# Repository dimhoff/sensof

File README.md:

# Sensof
Si4010 based wireless sensors(temperature, humidity, etc.) firmware and utilities.

**Project status**: This project is not actively maintained other then some
minor fixes to keep it working for myself.

# Sensof-HT
Sensof-HT is a temperature and humidity sensor that is build using a Si4010 MCU
and a HTU21 sensor.

## Circuit diagram
The Si4010 connects to a HTU21D, Si7020 or compatible sensor through I2C. The
I2C bus is connected to the Si4010 on the following pins:

   GPIO1 = SCL
   GPIO2 = SDA

Voltage level should be between 3.6 - 1.9 Volt. A 3V CR2032 works fine.

Some ready made Si4010 and HTU21D or Si7020 sensor are available on the
internet. These only need to be connected together and connected to a battery.

This repository also contains a custom Sensof-HT PCB. However this is currently
still under development. See hardware/README.md for more information.

## RF communication
The system uses the following modulation/encoding settings:

- Modulation: FSK
- Center Freq: 433.92 MHz
- FSK Deviation: 59 kHz
- Data rate: 9.6 kbits/s
- Encoding: NRZ Only (eg. no encoding)

## Receiver
I use a RFM22B module, which is based on the Si4430 transceiver,
connected to a Raspberry Pi for receiving the signal. The source code of the
receiving program is available in the software/si443x_sensof directory.

I also did some experiments with a SX1231 based module. Which seem to have a
better reception. I don't have any example code for this available in the
source tree.

# Sensof Frame Format
The Sensof frames are compatible with the Si4430/EZRadioPro receiver, and have
the following structure:

    +-----------+-----------+--------------+------------+
    | Preamble  | Sync Word | Enc. Payload | CRC-16-IBM |
    | 13 * 0xaa | 0x2d 0xd4 |   16-byte    |   2-byte   |
    +-----------+-----------+--------------+------------+

The CRC-16 uses the 0x8005 polynomial. The payload is a single AES-128
encrypted block, see [Encrypted Payload].

## Encrypted Payload
The payload is encrypted using AES-128 in ECB mode. To make this secure
against various attacks some mandatory field within the encrypted block have
been defined. The payload is formatted as follows:

    +---------+----------+------------------+
    | Dev. ID | Frame ID | Application data |
    | 4-byte  |  4-byte  |      8-byte      |
    +---------+----------+------------------+

The device ID identifies the source of the message. The Si4010 32-bit uniq
chip ID shall be used for this. The receiver will ignore frames that are from
an unknown source.

The 32-bit frame ID uniquely identifies the frame and allows duplicate frame
detection. The frame ID will be incremented sequentially, starting at 0. The
receiver must only accept frames with a frame ID above the last received frame
ID, and which is a 'reasonable amount higher' than the previous frame ID. See
the [Sensof Security Rational] chapter to get an indication of what a
'reasonable amount higher' means.

The remaining 8 byte can be used for application specific data. It is not
possible to have more or less then 8-byte payload in a single frame. If less
bytes are required the remaining bytes must be set to a known default. For
security reasons the receiver must verify these bytes. If more then 8 bytes
payload are required the payload must be split across multiple frames.

A full explanation of the security model is described below in [Sensof Security
Rational].

## Sensof-HT Frame Payload
The Sensof-HT frames contain the following payload:

 - Temperature(uint16_t): Temperature value as returned by HTU21 IC
 - Humidity(uint16_t): Humidity value as returned by HTU21 IC
 - Padding(uint32_t): '0' padding

See the HTU21 datasheet for the formulas to convert the temperature and
humidity to human readable values.

## SI4430 Compatibility
To receive the frames with the Si4430 receiver the following settings need to
be changed from the default configuration:

 - Header Length = 0
 - Fixed packet length = True
 - Packet length = 16

# Sensof Security Rational
The payload of all Sensof frames are encrypted to guarantee confidentiality and
integrity.

## Confidentiality
The AES algorithm is used with a 128-bit key. Since only a single block is
encrypted the strength of the encryption will be equal to that of the AES
algorithm.

All nodes in a system use the same pre-shared encryption key. This means that
if a single node in the system is suspected to be compromised the whole system
needs to be re-keyed.

## Integrity
The system depends on the avalanche effect of the AES block cipher protect
it integrity.

This means that if an adversary changes a single bit in the cipher text, that
the plain text changes completely and in an to the adversary unpredictable
manner.

By embedding known values into the encrypted blocks the receiver can verify
the decrypted data by checking if the known values are correct. In case of the
Sensof frames the device ID and frame ID are used for this. The change that an
adversary generates a frame that is accepted by the receiver would (probably)
be (somewhere in the order of):

    P = (N / 2^32) * (W / 2^32)

Where:
 N = Number of known nodes
 W = Size of accepted frame ID window

Of course any structure in the remaining 8 byte of payload will contribute to
this integrity protection. Therefor it is suggested to set any unused bytes to
'0', or any other fixed value, and verify these bytes on the receiver.

### Replay attack
To protect against replay attacks every frame has a 32-bit counter embedded.
The receiver must only accept frames with a frame ID above the last received
frame ID, and which is not more then a reasonable amount higher than the
previous frame ID.

In this case reasonable is the maximum amount of packets that one can expect to
be lost during normal operation.

It is essential that the receiver is initialized with the correct replay
counter at startup.  Just accepting the replay counter of the first received
frame as the current replay counter is not suggested. This allows an adversary
to replay a previously recorded stream of frames.

A suggested way is too let the receiver (periodically) store the current replay
counters per device and time to non-volatile storage. Upon restart of the
receiver these values should be read from storage and based on this the last
frame ID per device should be determined.
 In case of senders that send with a fix periodic interval this calculation can
be pretty accurate. For non-periodic senders other measures need to be taken
depending on the required security level.

If a sender losses its frame ID there are multiple possibilities:

 1. Reload node with expected frame ID based on the receiver's state
 2. Change the Device ID of the node
 3. Change the encryption key for the whole system

### Delay attack
In a delay attack the adversary provides the receiver with outdated
information. For example in a burglar alarm delaying the measurements of the
sensors for an hour would allow an adversary to break into the building with
the alarm only triggering after an hour.

To preform this attack the adversary would need to be able to prevent frames of
a node to reach the receiver, and record and replay those frames. This would
work if the receiver only relies on the frame ID from the frames to determine
the expected frame ID.

To prevent this attack for nodes that send packets with a fixed period the
receiver can protect against this by taking into account the frame interval,
current time and time of the last received frame to calculate what the expected
frame ID should be. Of course this system must leave some room for in accuracy
in the sending interval. But in general this should greatly reduce the attack
surface(Sorry, not going to prove statement this here...).

For nodes that do not have a periodic interval of sending frames the current
system does **NOT** offer any protection. If this is required an alternative
system where a time value is used instead of a frame ID can be considered.

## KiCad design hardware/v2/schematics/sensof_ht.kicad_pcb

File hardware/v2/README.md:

# Sensof HT v2 PCB (0003-00-00)
This is an experimental PCB for the Sensof HT nodes. Main features of this PCB
are:

 - Use a differential loop antenna
 - Have a properly placed test pads to build test bed

The differential loop antenna is cheap and is easy in assembly.

To allow testing and firmware loading access is required to some of the Si4010
pins. In this design is test pads are chosen. This eliminates the cost and
assembly of an extra connector that is only used during production. By placing
the test pads at a fixed pitch it should be easy to build a test bed with test
pins and a protoboard.

# Issues
PCB still has to be build and tested.

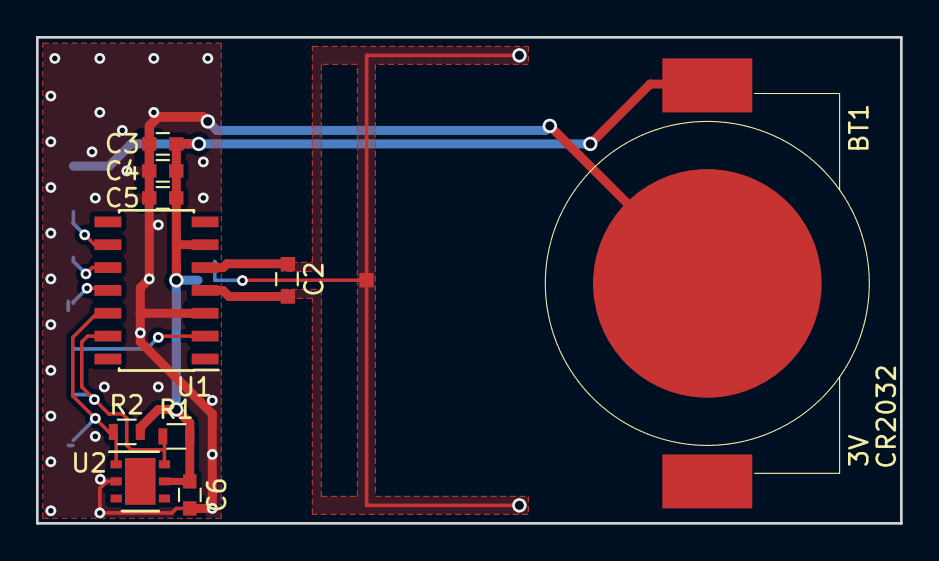
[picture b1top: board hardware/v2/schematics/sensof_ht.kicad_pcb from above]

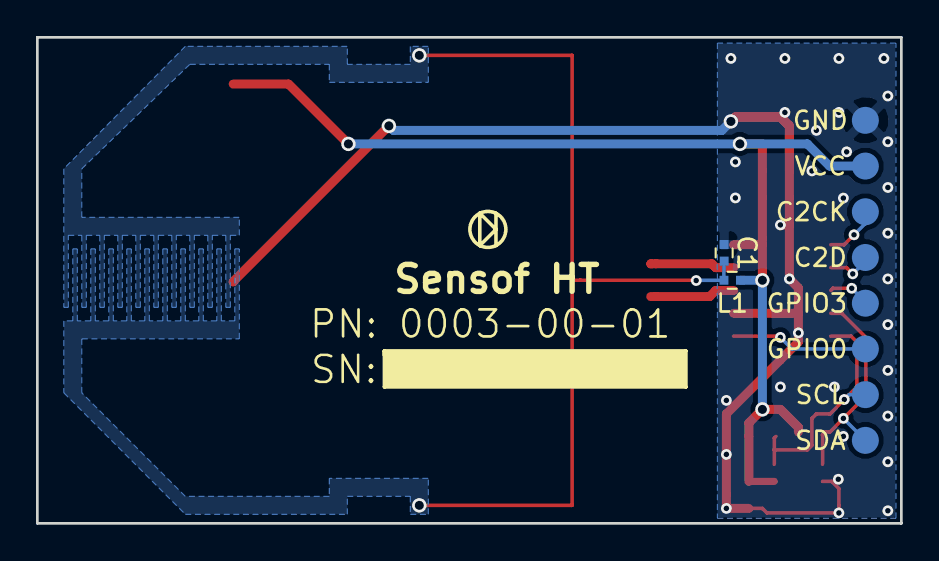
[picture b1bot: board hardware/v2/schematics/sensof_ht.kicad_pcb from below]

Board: 2 copper layers, 48.0 x 27.0 mm, 20 parts (10 on the bottom side), 9 nets.

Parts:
BT1: CR2032; silabs_cr2032
C1: 2.7pF; C_0402
C2: N.F.; C_0603
C3: 2.2uF; C_0603
C4: 1nF; C_0603
C5: 270pF; C_0603
C6: 100nF; C_0603
L1: 220nH; C_0402
R1, R2: 10k; R_0603
TP1: VCC; Measurement_Point_Round-SMD-Pad_Small-Labeled
TP2: SDA; Measurement_Point_Round-SMD-Pad_Small-Labeled
TP3: SCL; Measurement_Point_Round-SMD-Pad_Small-Labeled
TP4: GPIO0; Measurement_Point_Round-SMD-Pad_Small-Labeled
TP5: GPIO3; Measurement_Point_Round-SMD-Pad_Small-Labeled
TP6: C2D; Measurement_Point_Round-SMD-Pad_Small-Labeled
TP7: C2CK; Measurement_Point_Round-SMD-Pad_Small-Labeled
TP8: GND; Measurement_Point_Round-SMD-Pad_Small-Labeled
U1: Si4010-GT; SOIC-14_3.9x8.7mm_Pitch1.27mm
U2: HTU21D/Si7020; DFN-6-1EP_3x3mm_Pitch0.95mm

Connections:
GND: BT1.2, C1.1, C3.2, C4.2, C5.2, C6.2, TP8.1, U1.3, U2.2
unnamed: C1.2, C2.1, C2.2, L1.2, U1.4, U1.5
unnamed: R1.2, TP3.1, U1.13, U2.6
unnamed: R2.2, TP2.1, U1.12, U2.1
unnamed: TP4.1, U1.2
unnamed: TP5.1, U1.11
unnamed: TP6.1, U1.10
unnamed: TP7.1, U1.9
VDD: BT1.1, C3.1, C4.1, C5.1, C6.1, L1.1, R1.1, R2.1, TP1.1, U1.6, U2.5

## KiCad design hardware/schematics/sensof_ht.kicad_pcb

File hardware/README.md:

Sensof HT hardware
==================
Currently there are two PCB designs for the Sensof HT nodes:

 - v1: With on board 50 Ohm ceremic antenna
 - v2: With on board printed trace loop antenna

Sensof HT v1 PCB (0002-00-00)
=============================
This is an experimental PCB for the Sensof HT nodes. Main features of this PCB
are:

 - Uses a Ceramic 50 Ohm antenna + matching network
 - Has extensions connectors to connect to GPIO/I2C

The Ceramic antenna was chosen to see if it had a better range then a
differential loop antenna. It also allows for a smaller PCB.

The extension headers would allow other uses then just the Humidity/Temperature
sensor. And make it easier to experiment/develop with these modules.

Issues
-------
The following issues are found with the first prototype board(tag:
'hardware/0002-00-00')

### Range
The range of the is very limited. Apparently the antenna matching isn't optimal.

Replacing the antenna with a SMA connector, and then hooking the PCB up to a
HackRF through an attenuator, allowed for some simple tests.

This showed the output power to be relative high compared to a RFM60S. But the
power level is not very constant when sending a long pulse.

Doing a frequency sweep shows the power level is stable in the 300-400 MHz
range. I would have expected a spike around 434 MHz, like in AN369 "SI4010
Antenna Interface and Matching Network Guide"

### Assembly
The matching network makes assembly complicated and requires the device to be
reflow soldered.

### Price
The amount of quality components needed for antenna matching and the antenna it
self are relative expensive.

Sensof HT v2 PCB (0003-00-00)
=============================
This is an experimental PCB for the Sensof HT nodes. Main features of this PCB
are:

 - Use a differential loop antenna
 - Have a properly placed test pads to build test bed

The differential loop antenna is cheap and is easy in assembly.

To allow testing and firmware loading access is required to some of the Si4010
pins. In this design test pads are chosen. This eliminates the cost and
assembly of an extra connector that is only used during production. By placing
the test pads at a fixed pitch it should be easy to build a test bed with test
pins and a protoboard.

Issues
------
No serious issues were found with the first prototype board(tag:
'hardware/0003-00-00').

Range is comparable with the RFM60s based nodes I used before.

Only minor point is that the test points are spaced an 2.5 mm instead of 2.54
mm(0.1") but this within the acceptable margins.

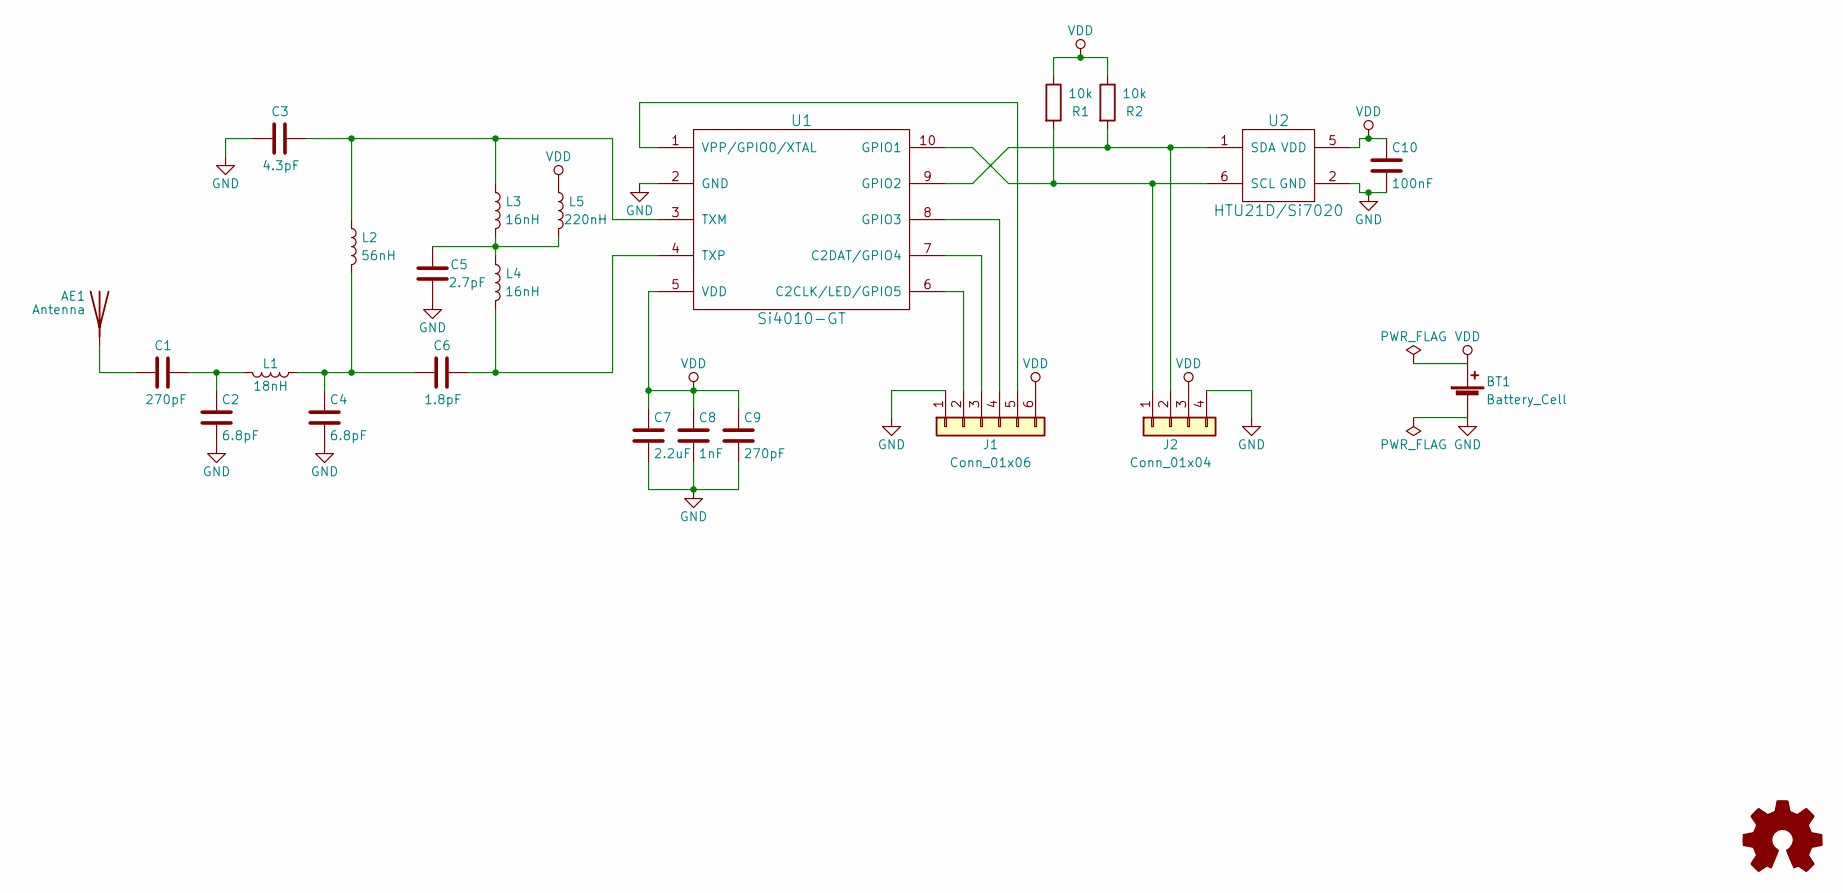
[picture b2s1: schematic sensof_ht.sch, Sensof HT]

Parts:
AE1: Antenna; ACAG1204-433-T
BT1: Battery_Cell; Linx_BAT-HLD-001
C1, C9: 270pF; C_0402
C2, C4: 6.8pF; C_0402
C3: 4.3pF; C_0402
C5: 2.7pF; C_0402
C6: 1.8pF; C_0402
C7: 2.2uF; C_0603
C8: 1nF; C_0402
C10: 100nF; C_0402
J1: Conn_01x06; JST_SH_SM06B-SRSS-TB_06x1.00mm_Angled
J2: Conn_01x04; JST_SH_SM04B-SRSS-TB_04x1.00mm_Angled
L1: 18nH; C_0402
L2: 56nH; C_0402
L3, L4: 16nH; C_0402
L5: 220nH; C_0402
R1, R2: 10k; R_0402
U1: Si4010-GT; MSOP-10_3x3mm_Pitch0.5mm
U2: HTU21D/Si7020; DFN-6-1EP_3x3mm_Pitch0.95mm

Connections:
GND: BT1.2 (-), C2.2, C3.2, C4.2, C5.1, C7.2, C8.2, C9.2, C10.2, J1.1, J2.4, U1.2 (GND), U2.2 (GND)
unnamed: AE1.1, C1.2
unnamed: C1.1, C2.1, L1.2
unnamed: C3.1, L2.1, L3.1, U1.3 (TXM)
unnamed: C4.1, C6.2, L1.1, L2.2
unnamed: C5.2, L3.2, L4.1, L5.2
unnamed: C6.1, L4.2, U1.4 (TXP)
unnamed: J1.2, U1.6 (C2CLK/LED/GPIO5)
unnamed: J1.3, U1.7 (C2DAT/GPIO4)
unnamed: J1.4, U1.8 (GPIO3)
unnamed: J1.5, U1.1 (VPP/GPIO0/XTAL)
unnamed: J2.1, R1.2, U1.10 (GPIO1), U2.6 (SCL)
unnamed: J2.2, R2.2, U1.9 (GPIO2), U2.1 (SDA)
VDD: BT1.1 (+), C7.1, C8.1, C9.1, C10.1, J1.6, J2.3, L5.1, R1.1, R2.1, U1.5 (VDD), U2.5 (VDD)

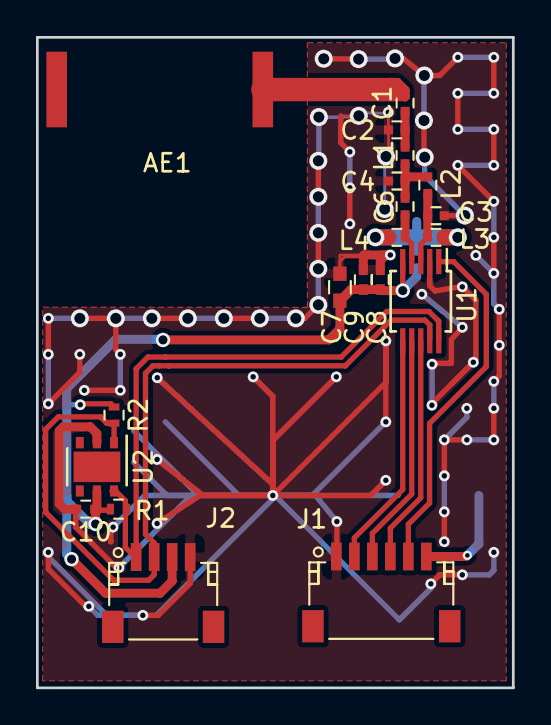
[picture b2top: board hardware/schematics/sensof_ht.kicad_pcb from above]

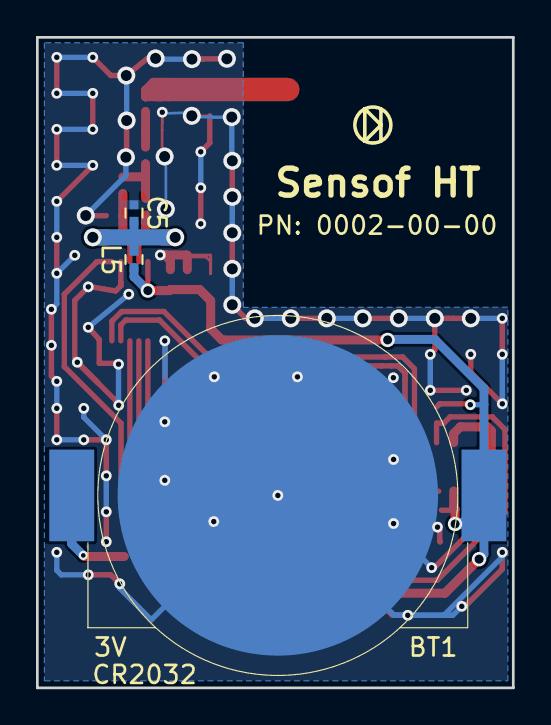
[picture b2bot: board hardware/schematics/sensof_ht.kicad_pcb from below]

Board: 2 copper layers, 26.4 x 36.1 mm, 23 parts (3 on the bottom side), 14 nets.

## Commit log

2015-01-18 Initial check-in
2015-04-15 Remove old OOK parameters
2015-04-15 Small cleanup and documentation
2015-04-15 Remove Header and Packet length from frame
2015-04-15 More documentation
2015-04-15 Increase packet counter to 32-bit
    Also created byte accessor to write/read packet counter to/from HVRAM.
    This save a lot in code size.
    Also don't increase packet counter if failed to read
    temperature/humidity.
2015-04-15 Add script to create NBF file from firmware
2015-07-11 Minor changes to comments
2015-07-11 Fix file permissions
2015-07-11 Some more documentation of protocol
2015-07-17 Remove crypto key file from GIT
2015-07-17 Add compile option to store replay counter in MTP
    By storing the packet counter in MTP the replay protection will also
    work across full power downs. This way we can change batteries without
    having to rekey or manually set the replay counter in HVRAM.
2015-07-17 Prepare for release v0.2.0
2016-04-15 Updated email address
2018-07-29 FW: Switch I2C pins to GPIO1/GPIO2
    Also disabled GPIO Matrix mode for this to work.
2018-08-17 FW: Update PA settings for Sensof HT (0002-00-00) board
    This also sets the output level to max.
2018-08-17 Added Sensof-HT PCB
2018-09-08 FW: add PA parameters for v2 PCB and lower level for v1
    For the v1 board use the max. that the calculation sheet allows.
2018-09-13 DOC: move inductor selection sheet into BOM sheet
2018-09-13 Si443x: Update Si443x regs to match calculation sheet output
    Change the TX address. This isn't used so not a functional
    change.
2018-09-13 HW: remove temporary BOM export files
2018-09-13 tools: Add Si443x based Sensof receivers
2018-09-13 si443x_sensof: Fine tune baud to calculated value.
    The wanted baud rate is 9600 but due to clock dividers the actual baud
    rate is 9590 baud. This was determined by the Si4010 calculation sheet.
2018-09-13 HW: Created a single README.md for both hardware designs
2018-09-13 Update symbol/footprints library
    Some small non functional updates to shared KiCad Library.
    Also updates the PCB board information with copyright etc.
2018-09-13 HW: update schematic information
    Just some textual update to schematic information fields.
    The current 0002-00-01 schematic has revision '01'. While the 0002-00-00
    schematic had revision '1'. This was a mistake, it should have been
    '00'. So '1' != '01'...
2018-09-13 HW: Set Si7020 as primary choice for sensor, and HTU21DF as alternative
    Switch this around since I prefer the Si7020.
2018-09-13 Update hardware Changelog
2018-09-13 HW: move Current PCB to V1 directory
2018-09-13 Si443x: Add correct register settings and calculation sheet
    This register settings uses the current packet format, with crc and
    without header.
2018-09-13 DOC: extend README.md
    Some more basic information about the construction of the hardware and
    the receiving side.
2018-09-13 HW: remove .bak backup files from repository
2018-09-13 RFM22b: Remove unmaintained receiver program
2018-09-13 HW: PCBv2 Upgraded to KiCad 5.0 and switch to shared component library
2018-09-13 HW: Updated V1 schematic to KiCad 5.0
2018-09-13 HW: Change fill zones and via's around matching network + add SN field
    Changed the fill zones and via's to much closer resemble the Silabs
    reference design. This also moves the C7/C8/C9 components.
    Also added a silkscreen box where the Serial number can be written down.
2018-09-13 HW: Update V1 schematic to use di_kicad_library and global library
    Import the di_kicad_library repository and swith the V1 schematic to use
    it. Also replace symbol for HTU21D with Si7020-A20 symbol from KiCad
    global library.
2018-09-13 HW: update CHANGES.md with new parts
2018-09-13 HW: Added Sensof HT v2 board
    New board with printed PCB antenna based on the 4010-DKMX-434 reference
    design.
2018-09-13 Add KiCad gitignore for hardware directory
2018-09-13 HW: Add readme for the different PCB designs
2018-09-15 PCBv2: Updated Test pad possitions
    Also removed a lot of ground traces that where there for the stitching
    via's. But it seems KiCad 5 is smart enough to recognize via's in a fill
    zone as belonging to that zone.
2018-09-15 PCBv2: add documentation of test pad possitions
2018-09-16 PCBv2: Cleanup unused libraries
    These components are now in KiCad or in di_kicad_library repository.
2018-09-16 PCBv2: Add part numbers to schematic
    Added part numbers from BOM to schematic.
2018-09-16 PCBv2: generated manufacturing files for PCB 0003-00-01
2018-09-16 PCBv2: Add part requirements to schematic
2018-09-16 PCBv2: Extended BOM with exact part specifications
2018-10-07 FW: Move firmware project file
    Moved file to get to a more uniform project layout
2018-10-07 FW: Only use abbreviated compiler flags
    Removed duplicate compiler flags. Only use the abbreviated form because
    the 'toolchain integration->customize' menu in the IDE only works with
    the short forms.
2018-11-07 HW: update CHANGES.md
2019-01-30 Added casing design for V2 PCB
2019-01-30 Added Programming/Test fixture for V2 PCB
2019-02-20 Reorder directories and add new .gitignore
    Bring it more inline with my other projects structure.
2019-02-20 HW: Added BOM suggestions to schematic for V1 hardware
    Add Manufacturer, mfr. no, mouser no fields to schematic.
2019-02-21 HW: rename partnumbers.txt -> PARTS.md
    Inline with other projects.
2019-02-21 HW: extend part number list with casing and bare PCB
2019-02-21 HW: Change part suggestions to the once I actually used in the prototype
2021-05-06 DOC: updated README.md with project status and RF parameters

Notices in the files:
hardware/v2/schematics/sensof_ht.kicad_pcb:
Copyright (c) 2018, David Imhoff
License: BSD-3-Clause
